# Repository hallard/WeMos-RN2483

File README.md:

ESP8266 WeMos Shield for microchip LORAWAN RN2483 or RN2903
===========================================================

This shield is used to hold [RN2483][4] Software with WeMos ESP8266 boards it has just few minimal features. 
- I2C Pullups placement
- Classic I2C 128x64 OLED connector
- Placement for Microchip LoraWan [RN2483][4] or [RN2903][4] module
- Placement for choosing single Wire, SMA or u-FL Antenna type for both 433MHz and 868MHz output
- Solder pad choosing 2 RX/TX available on ESP8266 (GPIO1/GPIO3 or GPIO13/GPIO12 to avoid conflict with onboard USB/Serial of WeMos)
- WS2812B Type LED for visual indication
- Custom switch on GPIO14

You can find more information on WeMos on their [site][1], it's really well documented. There is also a nice blog post on Microchip module made by disk91 [here][5]
I now use WeMos boards instead of NodeMCU's one because they're just smaller, features remains the same, but I also suspect WeMos regulator far better quality than the one used on NodeMCU that are just fake of originals AMS117 3V3.

**V1.1 Boards arrived from OSHPark, I tested them, worked out of the box but I made new revision cand corrected some mistakes**
V1.2 contain the following changes (board only, nothing chnaged on schematic):
- Added isolate ground pane to avoid sometime short between header and ground after soldering headers 
- Changed Silk to Node instead of gateway 

**V1.0 Boards arrived from OSHPark, I tested them, worked out of the box but I made new revision cand corrected some mistakes**
V1.1 contain the following changes:
- Error with RX/TX swapped on ESP8266, they are GPIO15/GPIO13 nor GPIO12/GPIO13 (so with V1.0 you can use SoftSerial or Native RX/TX of ESP but not in swapped mode)
- I made larger pad for Microchip module, even if I have strong experience in soldering in SMD, it was a pain to do them see picture below, I suspected board/solder. Ok made some new ones, think now I've got the technique ;-)
- Switch moved from GPIO14 to GPIO2, so I removed pullup because WeMos already have one on GPIO2
- Removed GPIO0 and GPIO11 from RN2483 to avoid as much as possible closer PAD

**V1.1 Boards are tested and working, waiting to test V1.2 but should works, just minor changes**

Detailed Description
====================

Look at the schematics for more informations.

### Firmware

Firmware is currently under developement and may not work as you expected, but for now it works fine for our testing lab.
It's available under [firmware folder][9]. See dedicated [README.md][10].

### Schematic

### Boards 
&nbsp;
&nbsp; 

You can order the PCB of this board at [OSHPARK][3] or at [PCBs.io][8]. But PCBs.io give me reward that allow me to buy some new created boards.

### Assembled boards (V1.0)

&nbsp;
&nbsp; 
&nbsp; 

##License

This work is licensed under a [Creative Commons Attribution-NonCommercial 4.0 International License](http://creativecommons.org/licenses/by-nc/4.0/)    
If you want to do commercial stuff with this project, please contact [CH2i company](https://www.ch2i.eu/en#support) so we can organize an simple agreement.

##Misc
See news and other projects on my [blog][2] 
 
[1]: http://www.wemos.cc/Products/d1_mini.html
[2]: https://hallard.me
[3]: https://oshpark.com/shared_projects/G3MI8Wk2
[4]: http://www.microchip.com/wwwproducts/Devices.aspx?product=RN2483
[5]: https://www.disk91.com/2015/technology/networks/first-step-in-lora-land-microchip-rn2483-test/
[6]: https://github.com/hallard/WebSocketToSerial
[7]: http://www.microchip.com/wwwproducts/Devices.aspx?product=RN2903
[8]: https://PCBs.io/share/zMbEp
[9]: https://github.com/hallard/WeMos-RN2483-firmware/tree/master/WeMos-rn2483
[10]: https://github.com/hallard/WeMos-RN2483-firmware/blob/master/WeMos-rn2483/README.md

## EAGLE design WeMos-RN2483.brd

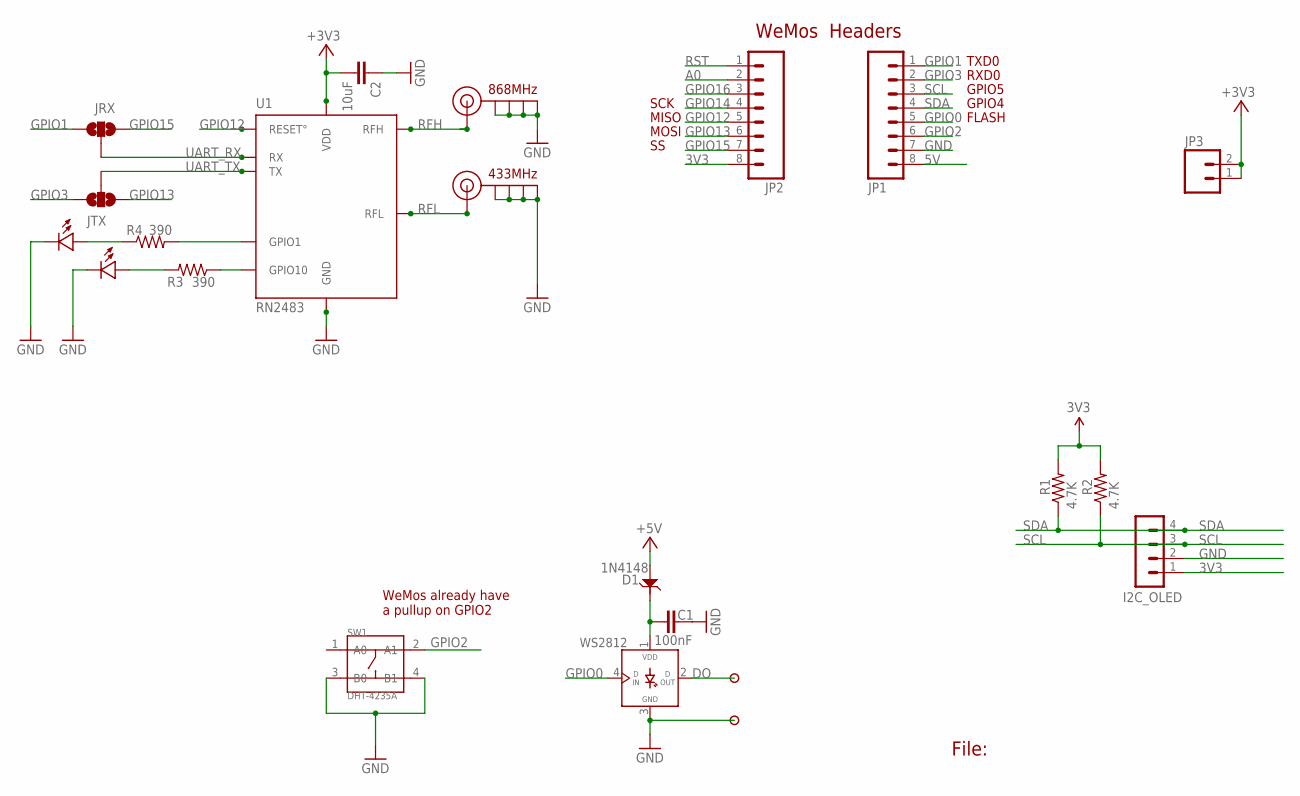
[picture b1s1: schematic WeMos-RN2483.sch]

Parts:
C1: 100nF; 0805-CAP
C2: 10uF; 0805-CAP-LARGEPADS
D1: 1N4148; SOD123-2.7X1.6
I2C_OLED: CON_HEADER_1X04'SMALL''; M1X4
J$1, J$3: ANTENNASMALL; SMA_UFL_PAD_SMALL
JP1, JP2: M08NO_SILK_FEMALE_PTH; 1X08_NO_SILK
JP3: M021X02_NO_SILK; 1X02_NO_SILK
JRX: JUMPER-PAD-3-NOFULL_BOX_SILK; PAD-JUMPER-3-NO_YES_SILK_FULL_BOX
JTX: JUMPER-PAD-3-NOFULL_BOX_SILK; PAD-JUMPER-3-NO_YES_SILK_FULL_BOX
P2, P3: PADNORMAL; PAD
R1, R2: 4.7K; 0805-RES
R3, R4: 390; 0805-RES
SW1: DHT-4235A; SW4-SMD-4.2X3.2X2.5MM
U1: RN2483; RN2483_4GPIO
U$2: GRN; 0805-LED
U$3: RED; 0805-LED
WS2812: WS2812B

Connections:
3V3: C2.2, I2C_OLED.1, JP2.8, JP3.1, JP3.2, R1.2, R2.2, U1.VDD, U1.VDD2 (VDD)
5V: D1.1, JP1.8
A0: JP2.2
DO: P2.1, WS2812.2 (DOUT)
GND: C1.2, C2.1, I2C_OLED.2, J$1.GND1 (GND), J$1.GND2 (GND), J$1.GND3 (GND), J$1.GND4 (GND), J$3.GND1 (GND), J$3.GND2 (GND), J$3.GND3 (GND), J$3.GND4 (GND), JP1.7, P3.1, SW1.3 (B0), SW1.4 (B1), U1.GND, U1.GND1 (GND), U1.GND2 (GND), U1.GND3 (GND), U1.GND4 (GND), U1.GND5 (GND), U1.GND6 (GND), U1.GND7 (GND), U1.GND8 (GND), U1.GND9 (GND), U1.GND10 (GND), U1.GND11 (GND), U1.GND12 (GND), U$2.MINUS, U$3.MINUS, WS2812.3 (GND)
GPIO0: JP1.5, WS2812.4 (DIN)
GPIO1: JP1.1, JRX.1
GPIO2: JP1.6, SW1.2 (A1)
GPIO3: JP1.2, JTX.3
GPIO12: JP2.5, U1.RESET°
GPIO13: JP2.6, JTX.1
GPIO14: JP2.4
GPIO15: JP2.7, JRX.3
GPIO16: JP2.3
unnamed: R4.2, U1.GPIO1
unnamed: R3.1, U1.GPIO10
unnamed: R3.2, U$3.PLUS
unnamed: R4.1, U$2.PLUS
RFH: J$3.ANT1 (SIGNAL), J$3.ANT2 (SIGNAL), U1.RFH
RFL: J$1.ANT1 (SIGNAL), J$1.ANT2 (SIGNAL), U1.RFL
RST: JP2.1
SCL: I2C_OLED.3, JP1.3, R2.1
SDA: I2C_OLED.4, JP1.4, R1.1
UART_RX: JRX.2, U1.UART_RX (RX)
UART_TX: JTX.2, U1.UART_TX (TX)
VLED: C1.1, D1.2, WS2812.1 (VDD)

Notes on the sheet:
File:
FLASH
MISO
GPIO4
GPIO5
RXD0
TXD0
MOSI
SCK
WeMos Headers
433MHz
868MHz
WeMos already have a pullup on GPIO2

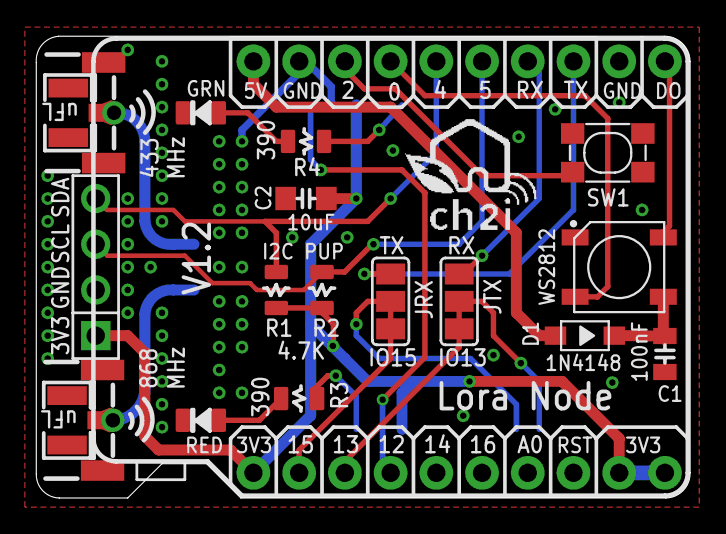
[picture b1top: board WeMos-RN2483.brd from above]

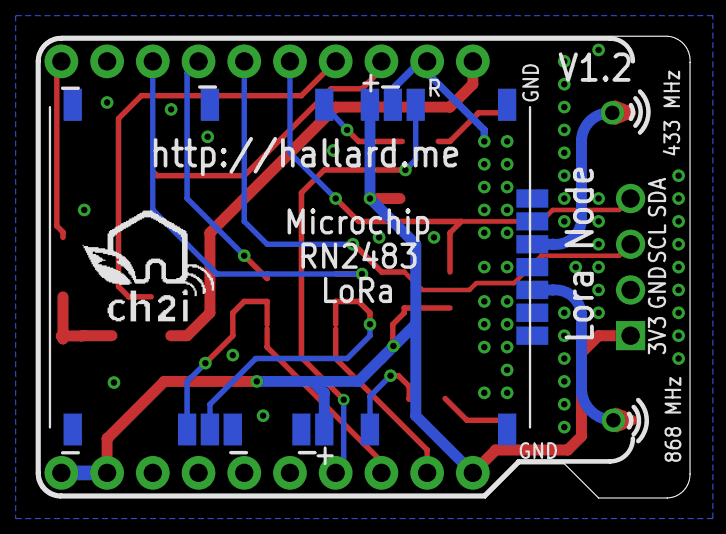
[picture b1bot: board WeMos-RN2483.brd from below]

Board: 2 copper layers, 36.3 x 25.7 mm, 24 parts (2 on the bottom side), 22 nets.

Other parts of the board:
U$1, U$4: LOGO_CH2I_75MM

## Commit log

2016-04-26 Creation
2016-04-26 Misnamed file
2016-04-26 added 2903
2016-04-26 ASP test
2016-04-26 Changed Name
2016-05-17 Version V1.1 update
2016-05-17 Added V1.1 description and pictures
2016-05-17 Added Firmware link
2016-05-22 Added picture of Web Console
2016-06-27 Added picture of assembled board
2016-06-27 Reduced 1st image size
2016-11-08 Changed silk Gateway to Node
2016-11-08 Added License and PCBs.io link
2016-11-08 Moved to pictures folder
2016-11-08 Updated to V1.1
2016-11-08 moved from top folder
2016-11-08 Changed pictures links
2016-11-08 Link error
2016-11-08 Added tested OK
2016-11-08 Updated to V1.2
2016-11-08 Bump to V1.2
2016-11-14 Corrected link error
2016-11-14 Fixed live link
2016-11-14 Updated sample config file
2016-11-14 Moved some screenshots to firmware README
2016-11-14 Added terminal screenshot
2016-11-14 Image Rotation
2016-11-14 Resized image
2016-11-14 Resize
2016-11-14 Removed image size
2017-09-06 moved firmware location

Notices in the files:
parts and their libraries:
SparkFun-Connectors: Licensing: Creative Commons ShareAlike 4.0 International - https://creativecommons.org/licenses/by-sa/4.0
